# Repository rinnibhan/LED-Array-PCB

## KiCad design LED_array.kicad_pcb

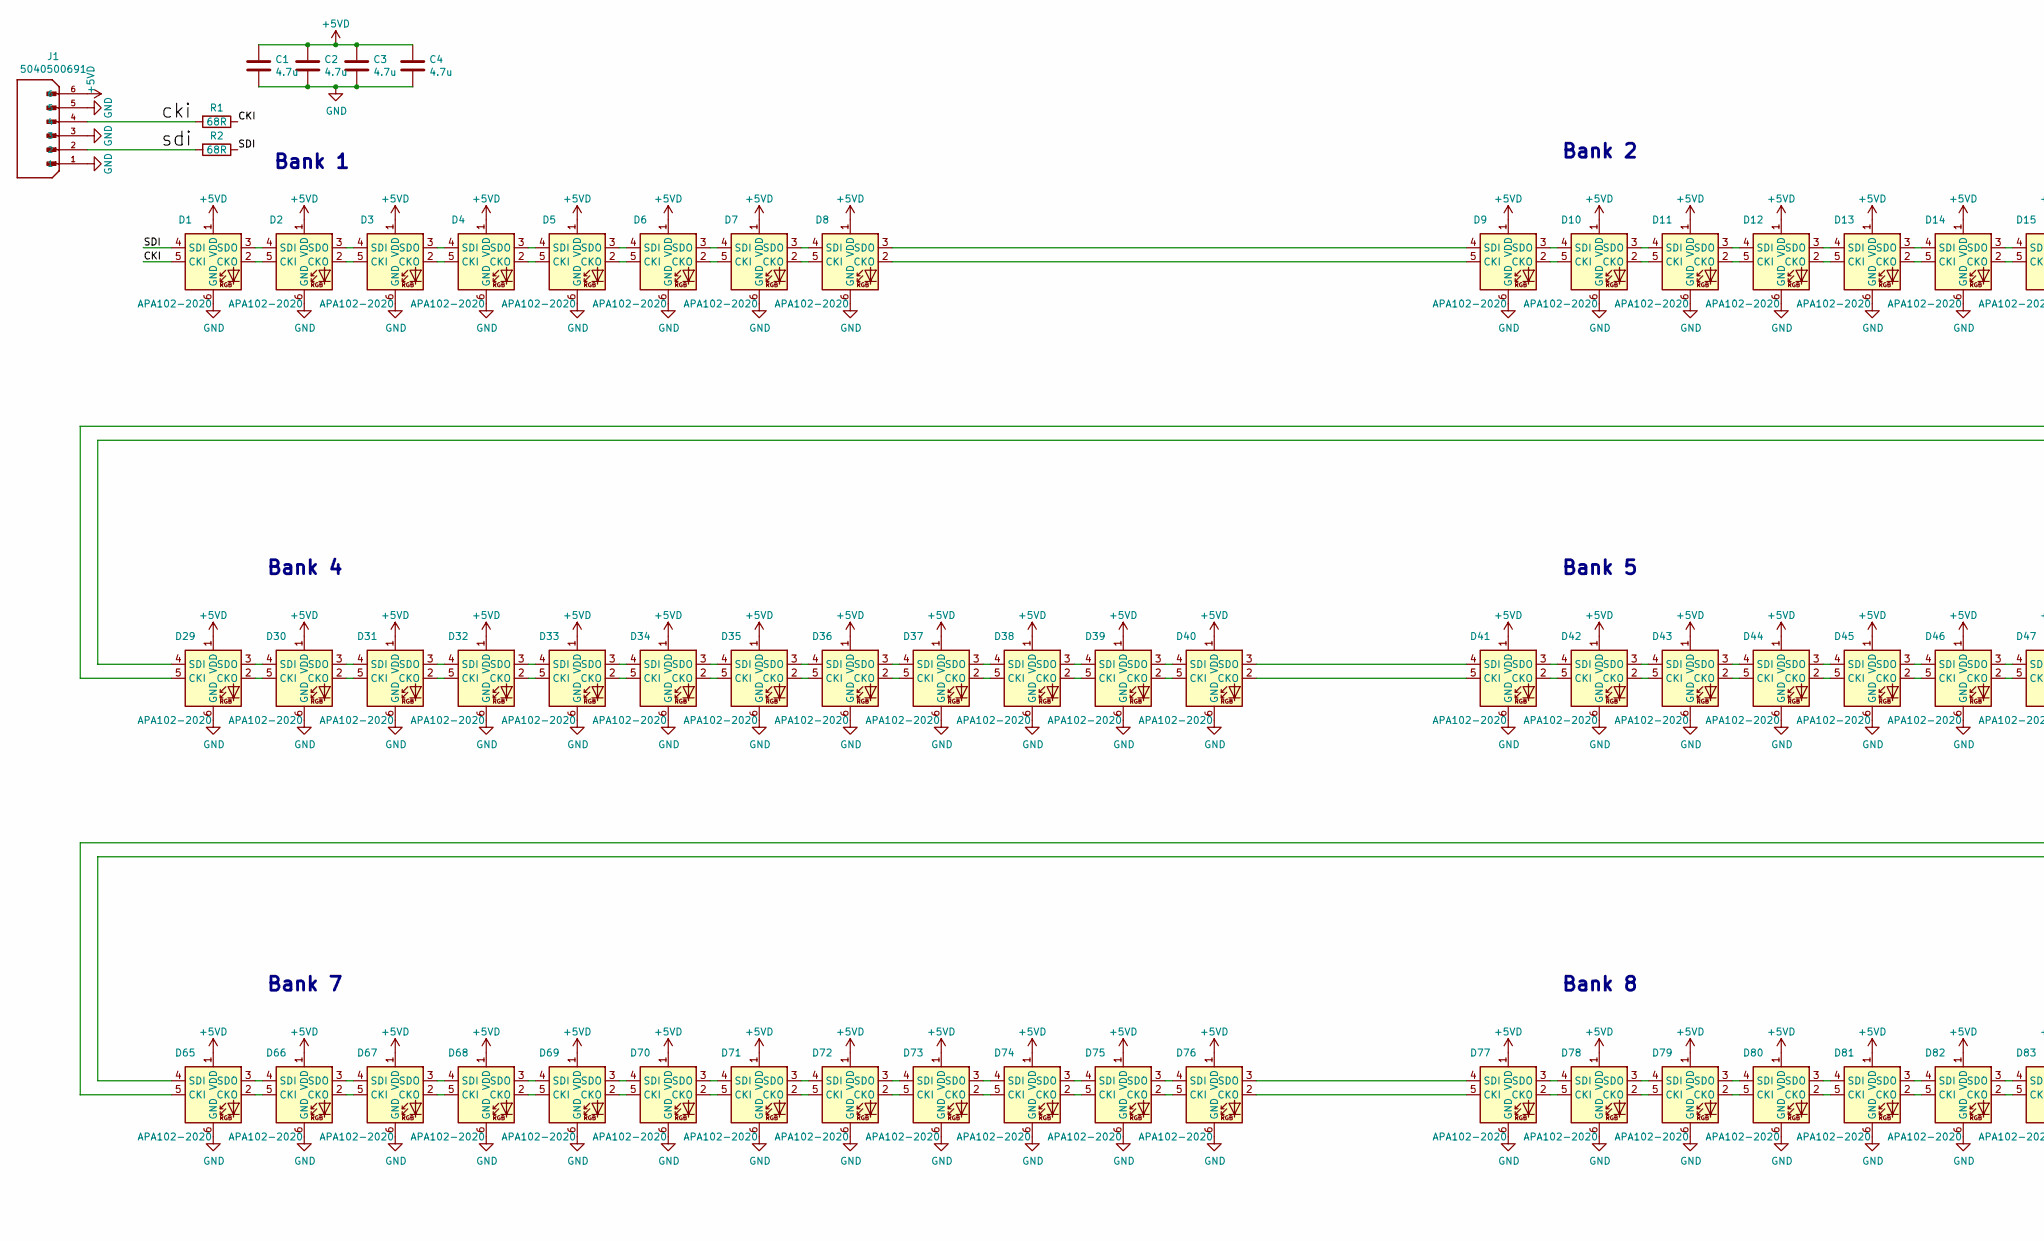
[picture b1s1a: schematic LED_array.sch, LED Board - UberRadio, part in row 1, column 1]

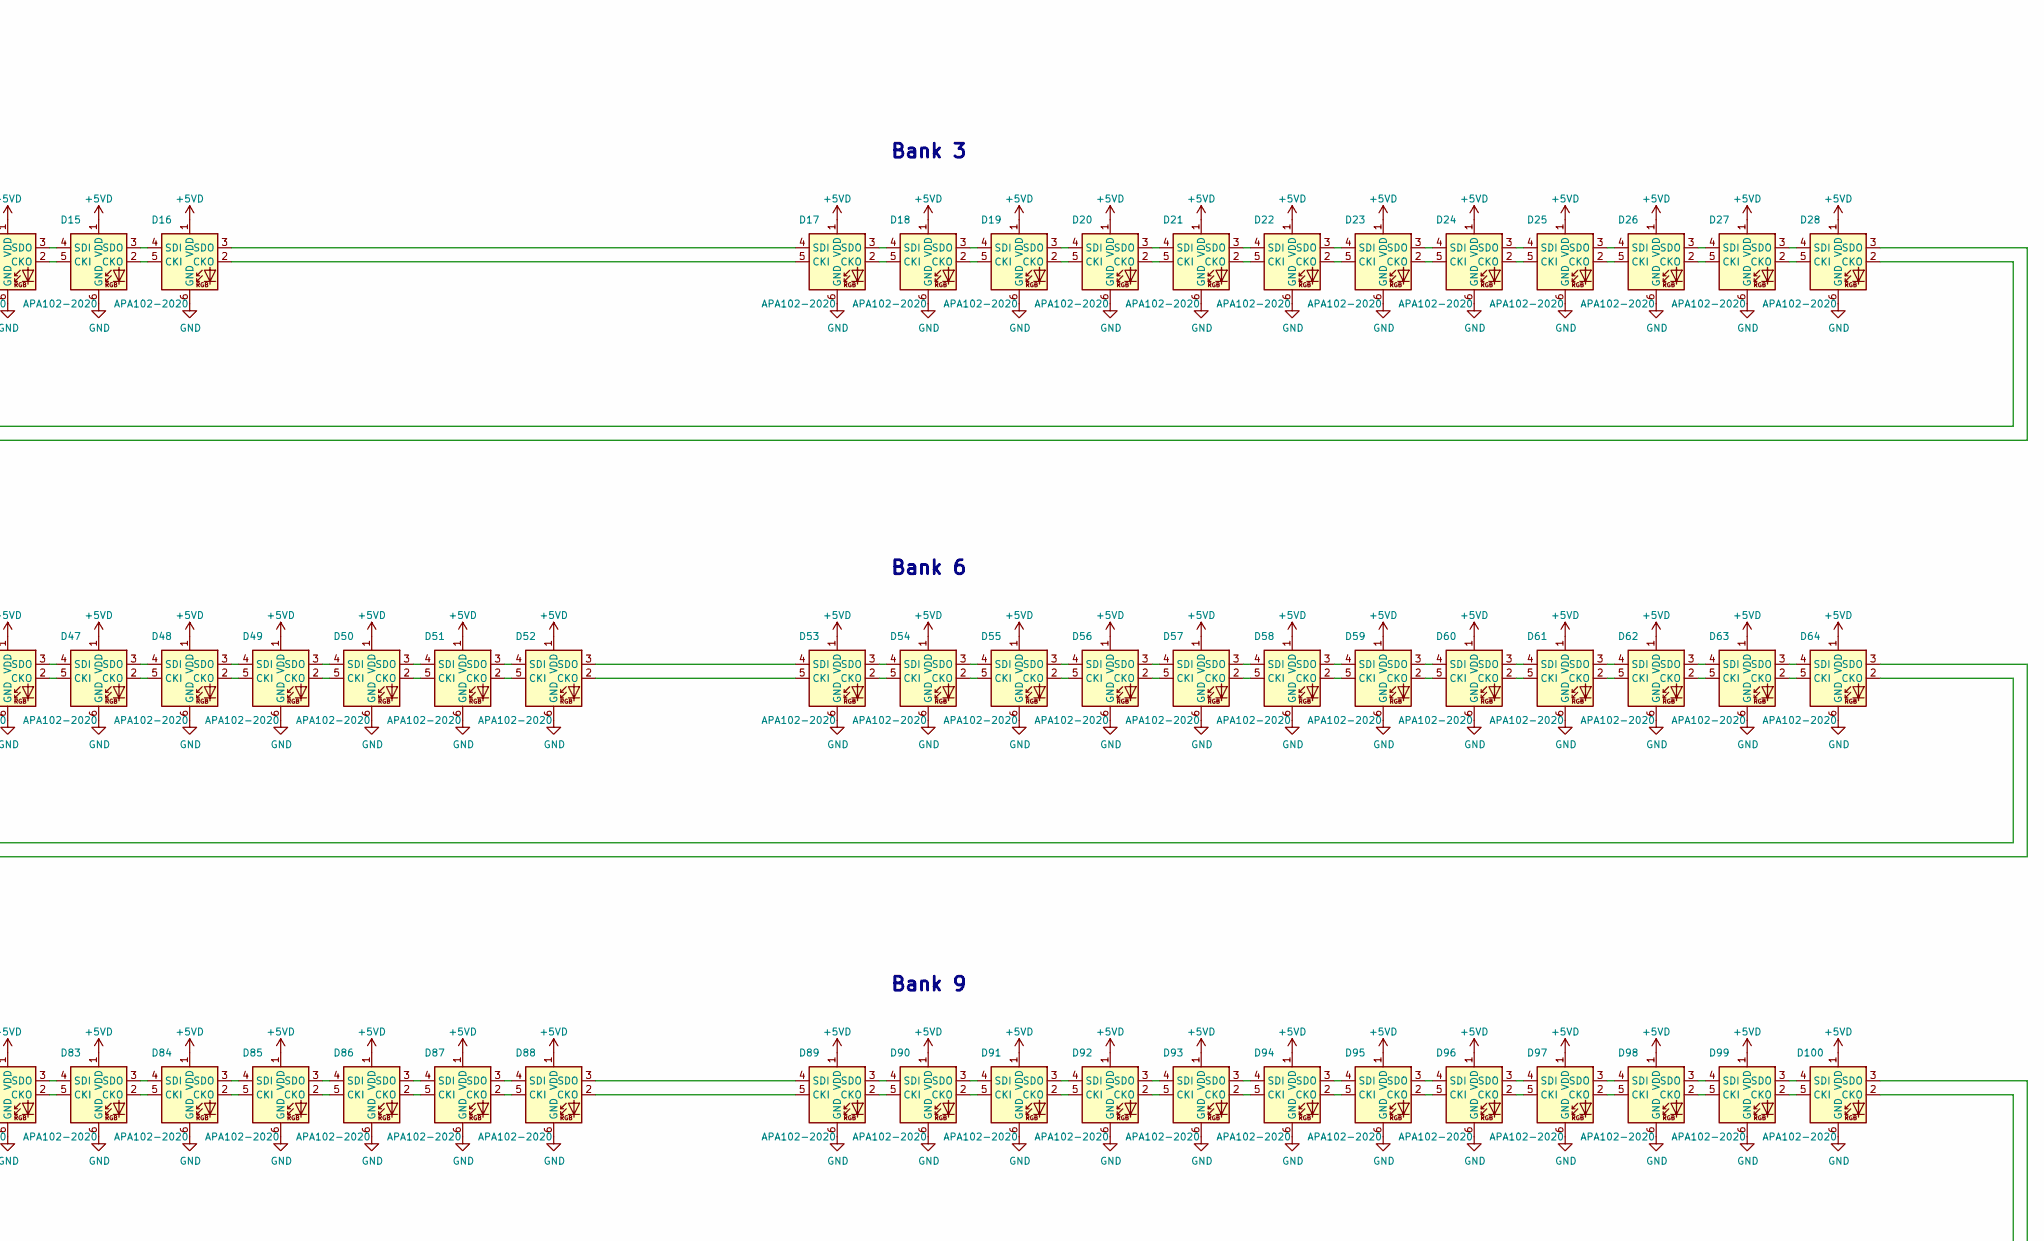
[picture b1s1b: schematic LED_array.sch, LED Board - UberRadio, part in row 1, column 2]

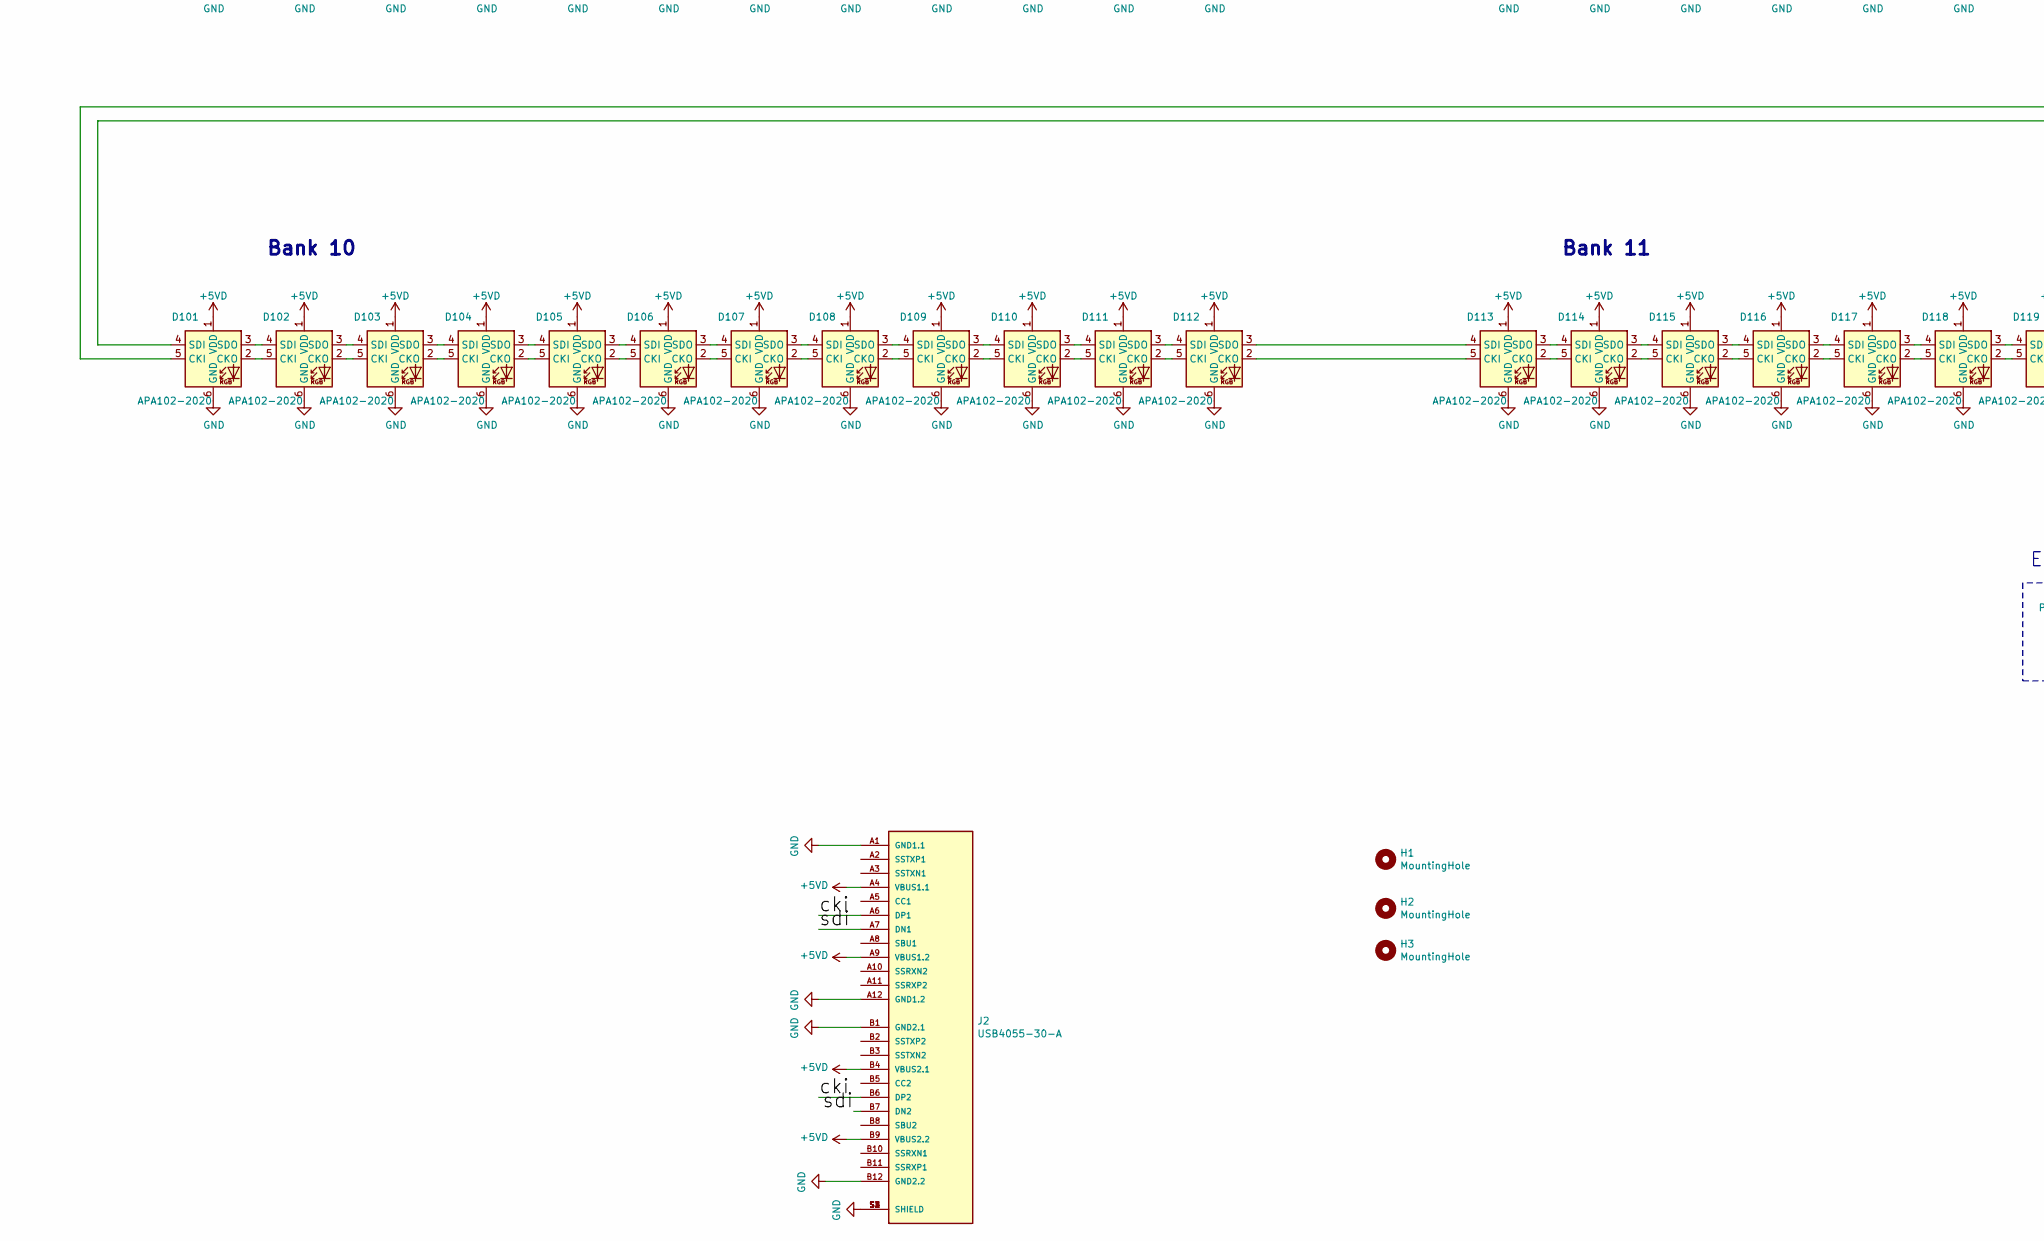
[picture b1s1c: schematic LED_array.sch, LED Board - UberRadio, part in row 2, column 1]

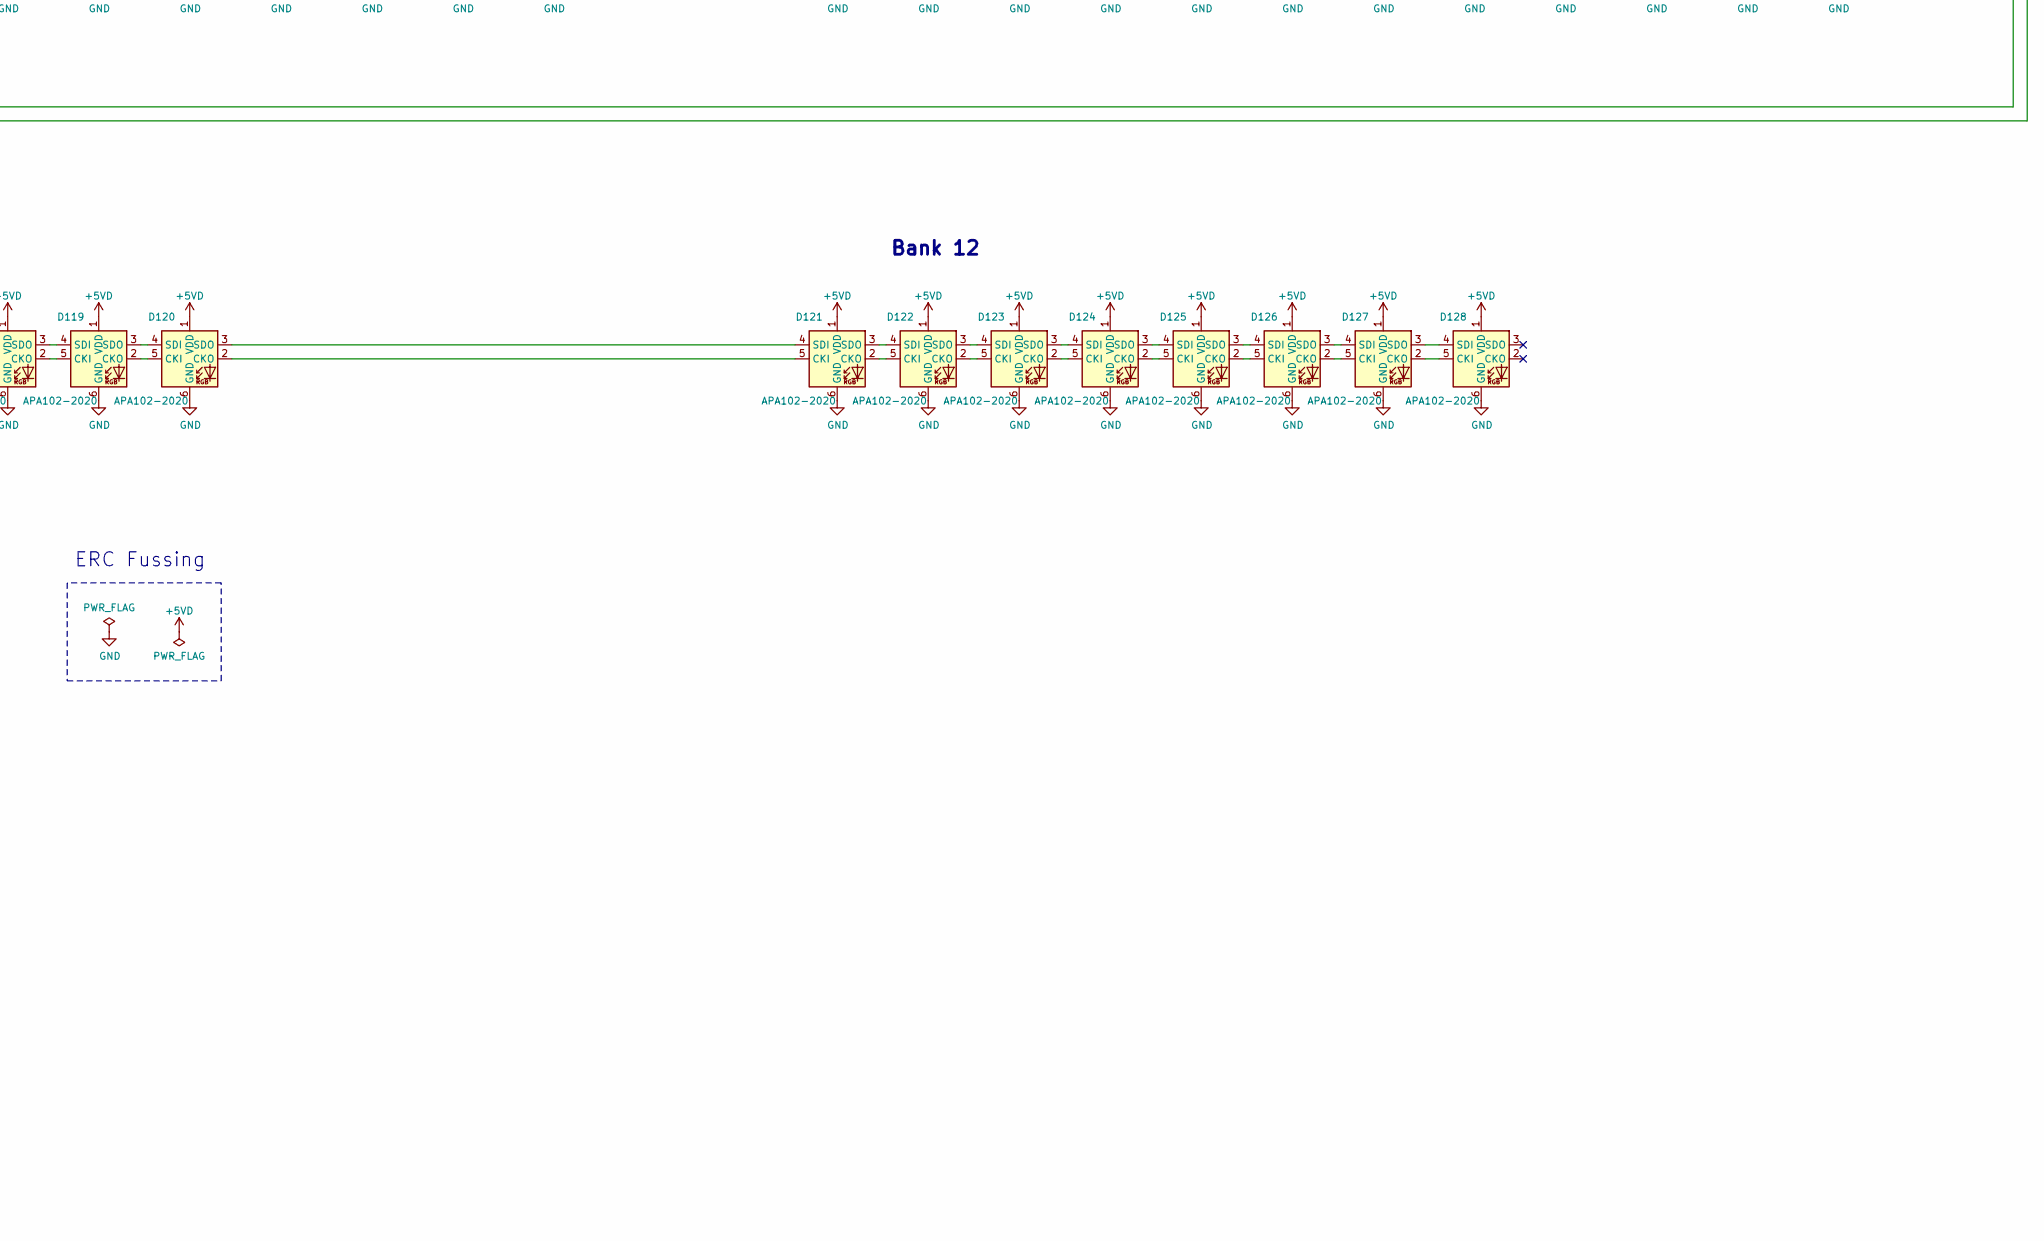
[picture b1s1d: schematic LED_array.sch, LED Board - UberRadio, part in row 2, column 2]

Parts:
C1, C2, C3, C4: 4.7u; C_1206_3216Metric
D1, D2, D3, D4, D5, D6, D7, D8, D9, D10, D11, D12, D13, D14, D15, D16, D17, D18, D19, D20, D21, D22, D23, D24, D25, D26, D27, D28, D29, D30, D31, D32, D33, D34, D35, D36, D37, D38, D39, D40, D41, D42, D43, D44, D45, D46, D47, D48, D49, D50, D51, D52, D53, D54, D55, D56, D57, D58, D59, D60, D61, D62, D63, D64, D65, D66, D67, D68, D69, D70, D71, D72, D73, D74, D75, D76, D77, D78, D79, D80, D81, D82, D83, D84, D85, D86, D87, D88, D89, D90, D91, D92, D93, D94, D95, D96, D97, D98, D99, D100, D101, D102, D103, D104, D105, D106, D107, D108, D109, D110, D111, D112, D113, D114, D115, D116, D117, D118, D119, D120, D121, D122, D123, D124, D125, D126, D127, D128: APA102-2020; LED-APA102-2020
H1, H2, H3: MountingHole; MountingHole_2mm
J1: 5040500691; MOLEX_5040500691; PARTREV B
J2: USB4055-30-A; GCT_USB4055-30-A; PARTREV B; DIGI-KEY_PART_NUMBER 2073-USB4055-30-ACT-ND
R1, R2: 68R; R_0603_1608Metric

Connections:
+5VD: C1.1, C2.1, C3.1, C4.1, D1.1 (VDD), D2.1 (VDD), D3.1 (VDD), D4.1 (VDD), D5.1 (VDD), D6.1 (VDD), D7.1 (VDD), D8.1 (VDD), D9.1 (VDD), D10.1 (VDD), D11.1 (VDD), D12.1 (VDD), D13.1 (VDD), D14.1 (VDD), D15.1 (VDD), D16.1 (VDD), D17.1 (VDD), D18.1 (VDD), D19.1 (VDD), D20.1 (VDD), D21.1 (VDD), D22.1 (VDD), D23.1 (VDD), D24.1 (VDD), D25.1 (VDD), D26.1 (VDD), D27.1 (VDD), D28.1 (VDD), D29.1 (VDD), D30.1 (VDD), D31.1 (VDD), D32.1 (VDD), D33.1 (VDD), D34.1 (VDD), D35.1 (VDD), D36.1 (VDD), D37.1 (VDD), D38.1 (VDD), D39.1 (VDD), D40.1 (VDD), D41.1 (VDD), D42.1 (VDD), D43.1 (VDD), D44.1 (VDD), D45.1 (VDD), D46.1 (VDD), D47.1 (VDD), D48.1 (VDD), D49.1 (VDD), D50.1 (VDD), D51.1 (VDD), D52.1 (VDD), D53.1 (VDD), D54.1 (VDD), D55.1 (VDD), D56.1 (VDD), D57.1 (VDD), D58.1 (VDD), D59.1 (VDD), D60.1 (VDD), D61.1 (VDD), D62.1 (VDD), D63.1 (VDD), D64.1 (VDD), D65.1 (VDD), D66.1 (VDD), D67.1 (VDD), D68.1 (VDD), D69.1 (VDD), D70.1 (VDD), D71.1 (VDD), D72.1 (VDD), D73.1 (VDD), D74.1 (VDD), D75.1 (VDD), D76.1 (VDD), D77.1 (VDD), D78.1 (VDD), D79.1 (VDD), D80.1 (VDD), D81.1 (VDD), D82.1 (VDD), D83.1 (VDD), D84.1 (VDD), D85.1 (VDD), D86.1 (VDD), D87.1 (VDD), D88.1 (VDD), D89.1 (VDD), D90.1 (VDD), D91.1 (VDD), D92.1 (VDD), D93.1 (VDD), D94.1 (VDD), D95.1 (VDD), D96.1 (VDD), D97.1 (VDD), D98.1 (VDD), D99.1 (VDD), D100.1 (VDD), D101.1 (VDD), D102.1 (VDD), D103.1 (VDD), D104.1 (VDD), D105.1 (VDD), D106.1 (VDD), D107.1 (VDD), D108.1 (VDD), D109.1 (VDD), D110.1 (VDD), D111.1 (VDD), D112.1 (VDD), D113.1 (VDD), D114.1 (VDD), D115.1 (VDD), D116.1 (VDD), D117.1 (VDD), D118.1 (VDD), D119.1 (VDD), D120.1 (VDD), D121.1 (VDD), D122.1 (VDD), D123.1 (VDD), D124.1 (VDD), D125.1 (VDD), D126.1 (VDD), D127.1 (VDD), D128.1 (VDD), J1.6, J2.A4 (VBUS1.1), J2.A9 (VBUS1.2), J2.B4 (VBUS2.1), J2.B9 (VBUS2.2)
/CKI: D1.5 (CKI), R1.1
/SDI: D1.4 (SDI), R2.1
/cki: J1.4, J2.A6 (DP1), J2.B6 (DP2), R1.2
/sdi: J1.2, J2.A7 (DN1), J2.B7 (DN2), R2.2
GND: C1.2, C2.2, C3.2, C4.2, D1.6 (GND), D2.6 (GND), D3.6 (GND), D4.6 (GND), D5.6 (GND), D6.6 (GND), D7.6 (GND), D8.6 (GND), D9.6 (GND), D10.6 (GND), D11.6 (GND), D12.6 (GND), D13.6 (GND), D14.6 (GND), D15.6 (GND), D16.6 (GND), D17.6 (GND), D18.6 (GND), D19.6 (GND), D20.6 (GND), D21.6 (GND), D22.6 (GND), D23.6 (GND), D24.6 (GND), D25.6 (GND), D26.6 (GND), D27.6 (GND), D28.6 (GND), D29.6 (GND), D30.6 (GND), D31.6 (GND), D32.6 (GND), D33.6 (GND), D34.6 (GND), D35.6 (GND), D36.6 (GND), D37.6 (GND), D38.6 (GND), D39.6 (GND), D40.6 (GND), D41.6 (GND), D42.6 (GND), D43.6 (GND), D44.6 (GND), D45.6 (GND), D46.6 (GND), D47.6 (GND), D48.6 (GND), D49.6 (GND), D50.6 (GND), D51.6 (GND), D52.6 (GND), D53.6 (GND), D54.6 (GND), D55.6 (GND), D56.6 (GND), D57.6 (GND), D58.6 (GND), D59.6 (GND), D60.6 (GND), D61.6 (GND), D62.6 (GND), D63.6 (GND), D64.6 (GND), D65.6 (GND), D66.6 (GND), D67.6 (GND), D68.6 (GND), D69.6 (GND), D70.6 (GND), D71.6 (GND), D72.6 (GND), D73.6 (GND), D74.6 (GND), D75.6 (GND), D76.6 (GND), D77.6 (GND), D78.6 (GND), D79.6 (GND), D80.6 (GND), D81.6 (GND), D82.6 (GND), D83.6 (GND), D84.6 (GND), D85.6 (GND), D86.6 (GND), D87.6 (GND), D88.6 (GND), D89.6 (GND), D90.6 (GND), D91.6 (GND), D92.6 (GND), D93.6 (GND), D94.6 (GND), D95.6 (GND), D96.6 (GND), D97.6 (GND), D98.6 (GND), D99.6 (GND), D100.6 (GND), D101.6 (GND), D102.6 (GND), D103.6 (GND), D104.6 (GND), D105.6 (GND), D106.6 (GND), D107.6 (GND), D108.6 (GND), D109.6 (GND), D110.6 (GND), D111.6 (GND), D112.6 (GND), D113.6 (GND), D114.6 (GND), D115.6 (GND), D116.6 (GND), D117.6 (GND), D118.6 (GND), D119.6 (GND), D120.6 (GND), D121.6 (GND), D122.6 (GND), D123.6 (GND), D124.6 (GND), D125.6 (GND), D126.6 (GND), D127.6 (GND), D128.6 (GND), J1.1, J1.3, J1.5, J2.A1 (GND1.1), J2.A12 (GND1.2), J2.B1 (GND2.1), J2.B12 (GND2.2), J2.S1 (SHIELD), J2.S2 (SHIELD), J2.S3 (SHIELD), J2.S4 (SHIELD)
unnamed: D1.2 (CKO), D2.5 (CKI)
unnamed: D1.3 (SDO), D2.4 (SDI)
unnamed: D2.2 (CKO), D3.5 (CKI)
unnamed: D2.3 (SDO), D3.4 (SDI)
unnamed: D3.2 (CKO), D4.5 (CKI)
unnamed: D3.3 (SDO), D4.4 (SDI)
unnamed: D4.2 (CKO), D5.5 (CKI)
unnamed: D4.3 (SDO), D5.4 (SDI)
unnamed: D5.2 (CKO), D6.5 (CKI)
unnamed: D5.3 (SDO), D6.4 (SDI)
unnamed: D6.2 (CKO), D7.5 (CKI)
unnamed: D6.3 (SDO), D7.4 (SDI)
unnamed: D7.2 (CKO), D8.5 (CKI)
unnamed: D7.3 (SDO), D8.4 (SDI)
unnamed: D8.2 (CKO), D9.5 (CKI)
unnamed: D8.3 (SDO), D9.4 (SDI)
unnamed: D10.2 (CKO), D11.5 (CKI)
unnamed: D10.3 (SDO), D11.4 (SDI)
unnamed: D9.3 (SDO), D10.4 (SDI)
unnamed: D9.2 (CKO), D10.5 (CKI)
unnamed: D11.2 (CKO), D12.5 (CKI)
unnamed: D11.3 (SDO), D12.4 (SDI)
unnamed: D12.2 (CKO), D13.5 (CKI)
unnamed: D12.3 (SDO), D13.4 (SDI)
unnamed: D13.2 (CKO), D14.5 (CKI)
unnamed: D13.3 (SDO), D14.4 (SDI)
unnamed: D14.2 (CKO), D15.5 (CKI)
unnamed: D14.3 (SDO), D15.4 (SDI)
unnamed: D15.2 (CKO), D16.5 (CKI)
unnamed: D15.3 (SDO), D16.4 (SDI)
unnamed: D16.2 (CKO), D17.5 (CKI)
unnamed: D16.3 (SDO), D17.4 (SDI)
unnamed: D17.2 (CKO), D18.5 (CKI)
unnamed: D17.3 (SDO), D18.4 (SDI)
unnamed: D18.2 (CKO), D19.5 (CKI)
unnamed: D18.3 (SDO), D19.4 (SDI)
unnamed: D19.2 (CKO), D20.5 (CKI)
unnamed: D19.3 (SDO), D20.4 (SDI)
unnamed: D20.2 (CKO), D21.5 (CKI)
unnamed: D20.3 (SDO), D21.4 (SDI)
unnamed: D21.2 (CKO), D22.5 (CKI)
unnamed: D21.3 (SDO), D22.4 (SDI)
unnamed: D22.2 (CKO), D23.5 (CKI)
unnamed: D22.3 (SDO), D23.4 (SDI)
unnamed: D23.2 (CKO), D24.5 (CKI)
unnamed: D23.3 (SDO), D24.4 (SDI)
unnamed: D24.2 (CKO), D25.5 (CKI)
unnamed: D24.3 (SDO), D25.4 (SDI)
unnamed: D25.2 (CKO), D26.5 (CKI)
unnamed: D25.3 (SDO), D26.4 (SDI)
unnamed: D26.2 (CKO), D27.5 (CKI)
unnamed: D26.3 (SDO), D27.4 (SDI)
unnamed: D27.2 (CKO), D28.5 (CKI)
unnamed: D27.3 (SDO), D28.4 (SDI)
unnamed: D28.2 (CKO), D29.5 (CKI)
unnamed: D28.3 (SDO), D29.4 (SDI)
unnamed: D29.2 (CKO), D30.5 (CKI)
unnamed: D29.3 (SDO), D30.4 (SDI)
unnamed: D30.2 (CKO), D31.5 (CKI)
unnamed: D30.3 (SDO), D31.4 (SDI)
unnamed: D31.2 (CKO), D32.5 (CKI)
unnamed: D31.3 (SDO), D32.4 (SDI)
unnamed: D32.2 (CKO), D33.5 (CKI)
unnamed: D32.3 (SDO), D33.4 (SDI)
unnamed: D33.2 (CKO), D34.5 (CKI)
unnamed: D33.3 (SDO), D34.4 (SDI)
unnamed: D34.2 (CKO), D35.5 (CKI)
unnamed: D34.3 (SDO), D35.4 (SDI)
unnamed: D35.2 (CKO), D36.5 (CKI)
unnamed: D35.3 (SDO), D36.4 (SDI)
unnamed: D36.2 (CKO), D37.5 (CKI)
unnamed: D36.3 (SDO), D37.4 (SDI)
unnamed: D37.2 (CKO), D38.5 (CKI)
unnamed: D37.3 (SDO), D38.4 (SDI)
unnamed: D38.2 (CKO), D39.5 (CKI)
unnamed: D38.3 (SDO), D39.4 (SDI)
unnamed: D39.2 (CKO), D40.5 (CKI)
unnamed: D39.3 (SDO), D40.4 (SDI)
unnamed: D40.2 (CKO), D41.5 (CKI)
unnamed: D40.3 (SDO), D41.4 (SDI)
unnamed: D41.2 (CKO), D42.5 (CKI)
unnamed: D41.3 (SDO), D42.4 (SDI)
unnamed: D42.2 (CKO), D43.5 (CKI)
unnamed: D42.3 (SDO), D43.4 (SDI)
unnamed: D43.2 (CKO), D44.5 (CKI)
unnamed: D43.3 (SDO), D44.4 (SDI)
unnamed: D44.2 (CKO), D45.5 (CKI)
unnamed: D44.3 (SDO), D45.4 (SDI)
unnamed: D45.2 (CKO), D46.5 (CKI)
unnamed: D45.3 (SDO), D46.4 (SDI)
unnamed: D46.2 (CKO), D47.5 (CKI)
unnamed: D46.3 (SDO), D47.4 (SDI)
unnamed: D47.2 (CKO), D48.5 (CKI)
unnamed: D47.3 (SDO), D48.4 (SDI)
unnamed: D48.2 (CKO), D49.5 (CKI)
unnamed: D48.3 (SDO), D49.4 (SDI)
unnamed: D49.2 (CKO), D50.5 (CKI)
unnamed: D49.3 (SDO), D50.4 (SDI)
unnamed: D50.2 (CKO), D51.5 (CKI)
unnamed: D50.3 (SDO), D51.4 (SDI)
unnamed: D51.2 (CKO), D52.5 (CKI)
unnamed: D51.3 (SDO), D52.4 (SDI)
unnamed: D52.2 (CKO), D53.5 (CKI)
unnamed: D52.3 (SDO), D53.4 (SDI)
unnamed: D53.2 (CKO), D54.5 (CKI)
unnamed: D53.3 (SDO), D54.4 (SDI)
unnamed: D54.2 (CKO), D55.5 (CKI)
unnamed: D54.3 (SDO), D55.4 (SDI)
unnamed: D55.2 (CKO), D56.5 (CKI)
unnamed: D55.3 (SDO), D56.4 (SDI)
unnamed: D56.2 (CKO), D57.5 (CKI)
unnamed: D56.3 (SDO), D57.4 (SDI)
unnamed: D57.2 (CKO), D58.5 (CKI)
unnamed: D57.3 (SDO), D58.4 (SDI)
unnamed: D58.2 (CKO), D59.5 (CKI)
unnamed: D58.3 (SDO), D59.4 (SDI)
unnamed: D59.2 (CKO), D60.5 (CKI)
unnamed: D59.3 (SDO), D60.4 (SDI)
unnamed: D60.2 (CKO), D61.5 (CKI)
unnamed: D60.3 (SDO), D61.4 (SDI)
unnamed: D61.2 (CKO), D62.5 (CKI)
unnamed: D61.3 (SDO), D62.4 (SDI)
unnamed: D62.2 (CKO), D63.5 (CKI)
unnamed: D62.3 (SDO), D63.4 (SDI)
unnamed: D63.2 (CKO), D64.5 (CKI)
unnamed: D63.3 (SDO), D64.4 (SDI)
unnamed: D64.2 (CKO), D65.5 (CKI)
unnamed: D64.3 (SDO), D65.4 (SDI)
unnamed: D65.2 (CKO), D66.5 (CKI)
unnamed: D65.3 (SDO), D66.4 (SDI)
unnamed: D66.2 (CKO), D67.5 (CKI)
unnamed: D66.3 (SDO), D67.4 (SDI)
unnamed: D67.2 (CKO), D68.5 (CKI)
unnamed: D67.3 (SDO), D68.4 (SDI)
unnamed: D68.2 (CKO), D69.5 (CKI)
unnamed: D68.3 (SDO), D69.4 (SDI)
unnamed: D69.2 (CKO), D70.5 (CKI)
unnamed: D69.3 (SDO), D70.4 (SDI)
unnamed: D70.2 (CKO), D71.5 (CKI)
unnamed: D70.3 (SDO), D71.4 (SDI)
unnamed: D71.2 (CKO), D72.5 (CKI)
unnamed: D71.3 (SDO), D72.4 (SDI)
unnamed: D72.2 (CKO), D73.5 (CKI)
unnamed: D72.3 (SDO), D73.4 (SDI)
unnamed: D73.2 (CKO), D74.5 (CKI)
unnamed: D73.3 (SDO), D74.4 (SDI)
unnamed: D74.2 (CKO), D75.5 (CKI)
unnamed: D74.3 (SDO), D75.4 (SDI)
unnamed: D75.2 (CKO), D76.5 (CKI)
unnamed: D75.3 (SDO), D76.4 (SDI)
unnamed: D76.2 (CKO), D77.5 (CKI)
unnamed: D76.3 (SDO), D77.4 (SDI)
unnamed: D77.2 (CKO), D78.5 (CKI)
unnamed: D77.3 (SDO), D78.4 (SDI)
unnamed: D78.2 (CKO), D79.5 (CKI)
unnamed: D78.3 (SDO), D79.4 (SDI)
unnamed: D79.2 (CKO), D80.5 (CKI)
unnamed: D79.3 (SDO), D80.4 (SDI)
unnamed: D80.2 (CKO), D81.5 (CKI)
unnamed: D80.3 (SDO), D81.4 (SDI)
unnamed: D81.2 (CKO), D82.5 (CKI)
unnamed: D81.3 (SDO), D82.4 (SDI)
unnamed: D82.2 (CKO), D83.5 (CKI)
unnamed: D82.3 (SDO), D83.4 (SDI)
unnamed: D83.2 (CKO), D84.5 (CKI)
unnamed: D83.3 (SDO), D84.4 (SDI)
unnamed: D84.2 (CKO), D85.5 (CKI)
unnamed: D84.3 (SDO), D85.4 (SDI)
unnamed: D85.2 (CKO), D86.5 (CKI)
unnamed: D85.3 (SDO), D86.4 (SDI)
unnamed: D86.2 (CKO), D87.5 (CKI)
unnamed: D86.3 (SDO), D87.4 (SDI)
unnamed: D87.2 (CKO), D88.5 (CKI)
unnamed: D87.3 (SDO), D88.4 (SDI)
unnamed: D88.2 (CKO), D89.5 (CKI)
unnamed: D88.3 (SDO), D89.4 (SDI)
unnamed: D89.2 (CKO), D90.5 (CKI)
unnamed: D89.3 (SDO), D90.4 (SDI)
unnamed: D90.2 (CKO), D91.5 (CKI)
unnamed: D90.3 (SDO), D91.4 (SDI)
unnamed: D91.2 (CKO), D92.5 (CKI)
unnamed: D91.3 (SDO), D92.4 (SDI)
unnamed: D92.2 (CKO), D93.5 (CKI)
unnamed: D92.3 (SDO), D93.4 (SDI)
unnamed: D93.2 (CKO), D94.5 (CKI)
unnamed: D93.3 (SDO), D94.4 (SDI)
unnamed: D94.2 (CKO), D95.5 (CKI)
unnamed: D94.3 (SDO), D95.4 (SDI)
unnamed: D95.2 (CKO), D96.5 (CKI)
unnamed: D95.3 (SDO), D96.4 (SDI)
unnamed: D96.2 (CKO), D97.5 (CKI)
unnamed: D96.3 (SDO), D97.4 (SDI)
unnamed: D97.2 (CKO), D98.5 (CKI)
unnamed: D97.3 (SDO), D98.4 (SDI)
unnamed: D98.2 (CKO), D99.5 (CKI)
unnamed: D98.3 (SDO), D99.4 (SDI)
unnamed: D100.2 (CKO), D101.5 (CKI)
unnamed: D100.3 (SDO), D101.4 (SDI)
unnamed: D99.3 (SDO), D100.4 (SDI)
unnamed: D99.2 (CKO), D100.5 (CKI)
unnamed: D101.2 (CKO), D102.5 (CKI)
unnamed: D101.3 (SDO), D102.4 (SDI)
unnamed: D102.2 (CKO), D103.5 (CKI)
unnamed: D102.3 (SDO), D103.4 (SDI)
unnamed: D103.2 (CKO), D104.5 (CKI)
unnamed: D103.3 (SDO), D104.4 (SDI)
unnamed: D104.2 (CKO), D105.5 (CKI)
unnamed: D104.3 (SDO), D105.4 (SDI)
unnamed: D105.2 (CKO), D106.5 (CKI)
unnamed: D105.3 (SDO), D106.4 (SDI)
unnamed: D106.2 (CKO), D107.5 (CKI)
unnamed: D106.3 (SDO), D107.4 (SDI)
unnamed: D107.2 (CKO), D108.5 (CKI)
unnamed: D107.3 (SDO), D108.4 (SDI)
unnamed: D108.2 (CKO), D109.5 (CKI)
unnamed: D108.3 (SDO), D109.4 (SDI)
unnamed: D109.2 (CKO), D110.5 (CKI)
unnamed: D109.3 (SDO), D110.4 (SDI)
unnamed: D110.2 (CKO), D111.5 (CKI)
unnamed: D110.3 (SDO), D111.4 (SDI)
unnamed: D111.2 (CKO), D112.5 (CKI)
unnamed: D111.3 (SDO), D112.4 (SDI)
unnamed: D112.2 (CKO), D113.5 (CKI)
unnamed: D112.3 (SDO), D113.4 (SDI)
unnamed: D113.2 (CKO), D114.5 (CKI)
unnamed: D113.3 (SDO), D114.4 (SDI)
unnamed: D114.2 (CKO), D115.5 (CKI)
unnamed: D114.3 (SDO), D115.4 (SDI)
unnamed: D115.2 (CKO), D116.5 (CKI)
unnamed: D115.3 (SDO), D116.4 (SDI)
unnamed: D116.2 (CKO), D117.5 (CKI)
unnamed: D116.3 (SDO), D117.4 (SDI)
unnamed: D117.2 (CKO), D118.5 (CKI)
unnamed: D117.3 (SDO), D118.4 (SDI)
unnamed: D118.2 (CKO), D119.5 (CKI)
unnamed: D118.3 (SDO), D119.4 (SDI)
unnamed: D119.2 (CKO), D120.5 (CKI)
unnamed: D119.3 (SDO), D120.4 (SDI)
unnamed: D120.2 (CKO), D121.5 (CKI)
unnamed: D120.3 (SDO), D121.4 (SDI)
unnamed: D121.2 (CKO), D122.5 (CKI)
unnamed: D121.3 (SDO), D122.4 (SDI)
unnamed: D122.2 (CKO), D123.5 (CKI)
unnamed: D122.3 (SDO), D123.4 (SDI)
unnamed: D123.2 (CKO), D124.5 (CKI)
unnamed: D123.3 (SDO), D124.4 (SDI)
unnamed: D124.2 (CKO), D125.5 (CKI)
unnamed: D124.3 (SDO), D125.4 (SDI)
unnamed: D125.2 (CKO), D126.5 (CKI)
unnamed: D125.3 (SDO), D126.4 (SDI)
unnamed: D126.2 (CKO), D127.5 (CKI)
unnamed: D126.3 (SDO), D127.4 (SDI)
unnamed: D127.2 (CKO), D128.5 (CKI)
unnamed: D127.3 (SDO), D128.4 (SDI)

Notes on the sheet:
Bank 4
Bank 1
Bank 10
Bank 5
Bank 6
Bank 2
Bank 3
Bank 7
ERC Fussing
Bank 12
Bank 11
Bank 8
Bank 9

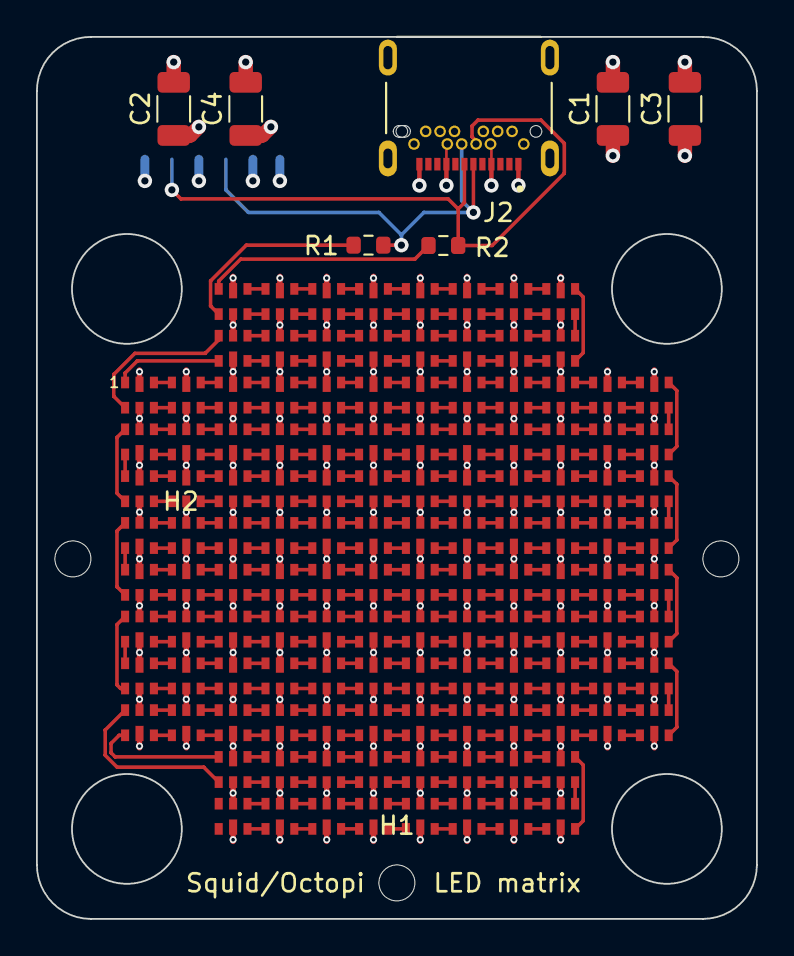
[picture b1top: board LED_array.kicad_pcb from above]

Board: 4 copper layers, 40.0 x 49.0 mm, 139 parts (1 on the bottom side), 260 nets.

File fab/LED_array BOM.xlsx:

LED_array
Id | Designator | Package | Quantity | Designation | Supplier and ref
1 | J1 | MOLEX_5040500691 | 1 | 5040500691
2 | D121,D1,D2,D3,D4,D5,D6,D7,D8,D9,D10,D11,D12,D13,D14,D15,D16,D17,D18,D19,D20,D21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 | LED-APA102-2020 | 128 | APA102-2020
3 | C4,C3,C2,C1 | C_1206_3216Metric | 4 | 4.7u
4 | R2,R1 | R_0603_1608Metric | 2 | 68R

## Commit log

2021-03-23 LED Array
    TODO: Unsure of power plane/connector placement
2021-03-29 finalized LED
2021-03-29 adding untracked files
2021-03-29 Adding in resistors and capacitor pads
2021-04-12 minor edits + generation of fab files edits: (1) add capacitors (2) change via and track size for the picolock conenctor (3) update the picolock connector footprint for handsoldering (4) remove label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
2021-04-13 final export
2021-04-13 additional commit post closing the program
2022-03-05 uodate 5/4/2021
2022-03-05 v2 - add a USB-C connector
2022-05-10 footprint update
